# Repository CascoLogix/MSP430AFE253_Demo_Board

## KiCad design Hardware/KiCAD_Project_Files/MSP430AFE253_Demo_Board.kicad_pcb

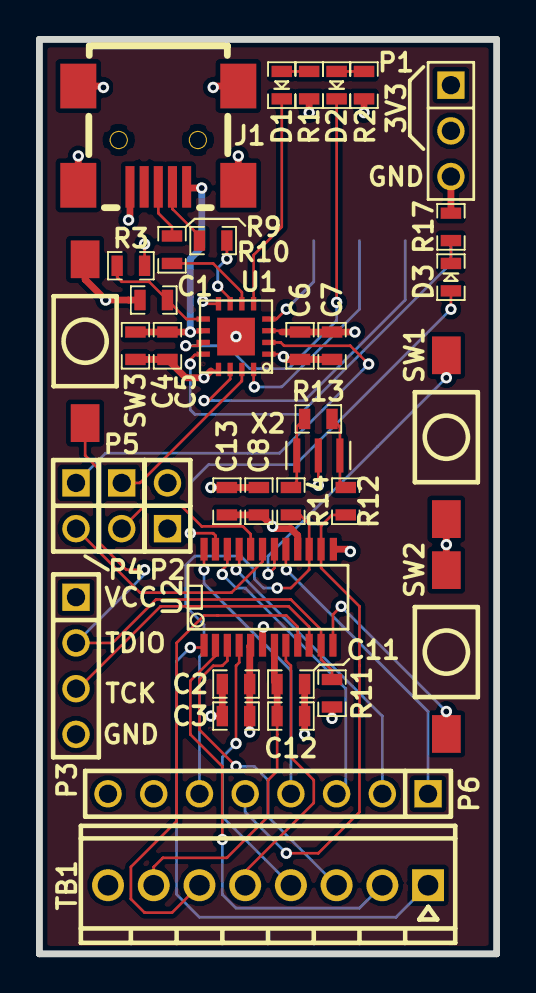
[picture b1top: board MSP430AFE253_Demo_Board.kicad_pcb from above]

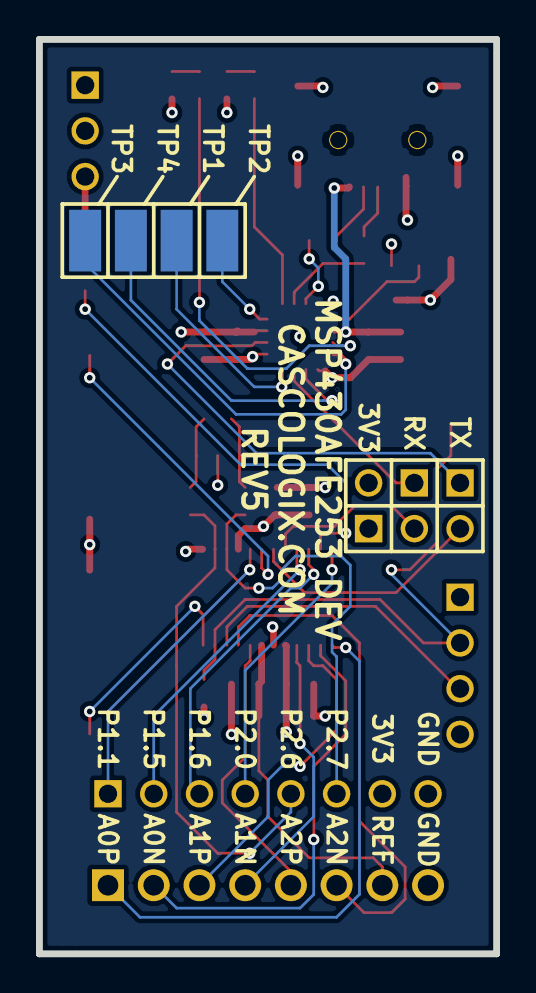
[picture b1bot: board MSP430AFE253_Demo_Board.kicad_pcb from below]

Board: 4 copper layers, 25.4 x 50.8 mm, 42 parts (4 on the bottom side), 42 nets.

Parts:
C1, C2, C5, C6, C11, C13: 0.1u; 0603
C3, C4, C7, C8, C12: 4.7u; 0603
D1: GRN; D0603
D2: RED; D0603
D3: BLUE; D0603
J1: USB_MINI_B; USB_MINI_B_RA_SMT
P1: POWER; HEADER_100MIL_1R3P_PTH
P2: 3.3V; HEADER_100MIL_1R2P_PTH
P3: HEADER_1X4; HEADER_100MIL_1R4P_PTH
P4: TX; HEADER_100MIL_1R2P_PTH
P5: RX; HEADER_100MIL_1R2P_PTH
P6: DEBUG; HEADER_100MIL_1R8P_PTH
R1, R2: 270; 0603
R3, R11: 47k; 0603
R9, R10: 33; 0603
R12, R14: 0; 0603
R13: 1M; 0603
R17: 750; 0603
SW1, SW2, SW3: FSMSM
TB1: ANALOG; TB_100MIL_1R8P_PTH
TP1, TP2, TP3, TP4: 5015; TP_PAD_SMT_5015
U1: FT230XQ; QFN-16_4MM_0.65MM
U2: MSP430AFE253; SSOP24
X2: 8MHz; CER_RES_1.2MM_SMT

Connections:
+5V: C4.1, C5.1, J1.1, U1.10
/A0N: TB1.2, U2.2
/A0P: TB1.1, U2.1
/A1N: TB1.4, U2.4
/A1P: TB1.3, U2.3
/A2N: TB1.6, U2.9
/A2P: TB1.5, U2.8
/P1.1: P6.1, U2.17
/P1.5: P6.2, U2.21
/P1.6: P6.3, U2.22
/P2.0: P6.4, U2.24
GND: C1.2, C2.2, C3.2, C4.2, C5.2, C6.2, C7.2, C8.2, C11.2, C12.2, C13.2, J1.5, J1.6, J1.7, J1.8, J1.9, P1.3, P3.4, P6.8, R17.2, SW1.2, SW2.2, SW3.2, TB1.8, U1.3, U1.13, U1.17, U2.6, U2.13, X2.2
unnamed: R12.1, R13.1, X2.1
unnamed: R9.2, U1.6
unnamed: R10.2, U1.7
unnamed: SW2.1, U2.12
unnamed: P5.2, U2.20
unnamed: J1.2, R10.1
unnamed: TP4.1, U1.14
unnamed: C1.1, R3.2, U1.9
unnamed: SW1.1, U2.18
unnamed: TP1.1, U1.16
unnamed: TP2.1, U1.4
unnamed: TP3.1, U1.12
unnamed: R13.2, R14.1, X2.3
unnamed: D2.C, U1.11
unnamed: P4.1, U1.2
unnamed: P5.1, U1.15
unnamed: C11.1, C12.1, TB1.7, U2.7
unnamed: P3.3, U2.10
unnamed: D1.C, U1.5
unnamed: D2.A, R2.2
unnamed: D1.A, R1.2
unnamed: D3.C, R17.1
unnamed: P3.2, R11.2, SW3.1, U2.11
unnamed: P4.2, U2.19
unnamed: J1.3, R9.1
unnamed: D3.A, U2.23
VCC: C2.1, C3.1, C8.1, C13.1, P1.1, P1.2, P2.1, P3.1, P6.7, R11.1, U2.5, U2.16
VCCIO: C6.1, C7.1, P2.2, R1.1, R2.1, R3.1, U1.1, U1.8
XT2IN: P6.5, R12.2, U2.14
XT2OUT: P6.6, R14.2, U2.15

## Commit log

2012-09-30 First KiCAD project commit
2012-09-30 Updated VCC track to go between header pins of RX & TX headers instead of around the outside near PCB edge. This allowed the GND plane (filled zone) to connect the GND pins of P3, P6, and TB1.
2012-09-30 Updated per VCC track change to route track through middle of RX & TX header pins instead of around outside near PCB edge.
2012-11-06 First commmit after implementing standard project directory structure.
2012-12-11 Rev'd board design and schematic to utilize smaller-footprint 8MHz crystal resonators.
2013-01-12 Minor changes
2013-02-26 Corrected the Libraries directory in the project file to point to the correct file path Corrected the 3D model file paths in the board file to point to the correct 3D model directories
2013-02-26 Updated PCB footprints to reference proper 3D LED components
2013-10-21 Updated to new kicad board format + Rendered pics
2013-11-04 The Freescale USB-to-Serial IC seems to be obsolee. This is a baseline check-in before changing to the FTDI FT230XQ.
2013-11-04 One file hadn't been saved prior to the previous check-in.
2014-07-27 Rev 3 release
2014-07-27 Clean up repo directory structure
2014-07-27 Converted to git from hg
2014-07-27 First commit as git repo
2014-08-15 First commit at Rev 4
2014-08-15 Removed files inadvertently added in previous commit
2014-08-15 Removed OSH Park Order Details file
2014-08-15 Updated Schematic and Board design for corrected TX LED connection
2014-08-23 Check in current state of Rev 4 design (in-progress) before checking out and forking the Rev 1 design.
2014-08-23 Final commit for Rev4 release
2014-08-23 Forgot to update rev info on back silkscreen
2014-08-27 Found quantity errors on BOM after last check in for Rev changes. Also added transparent background pics of 3D PCB assembly render.
2014-09-19 Rev 5 Commit. Generated new board gerbers and drawings. Updated user guide documentation and board renderings.
2014-09-22 Added datasheets.
    Updated PCB file to call out correct parts for 3D view.
2014-10-06 Updated document revision located in footer.
